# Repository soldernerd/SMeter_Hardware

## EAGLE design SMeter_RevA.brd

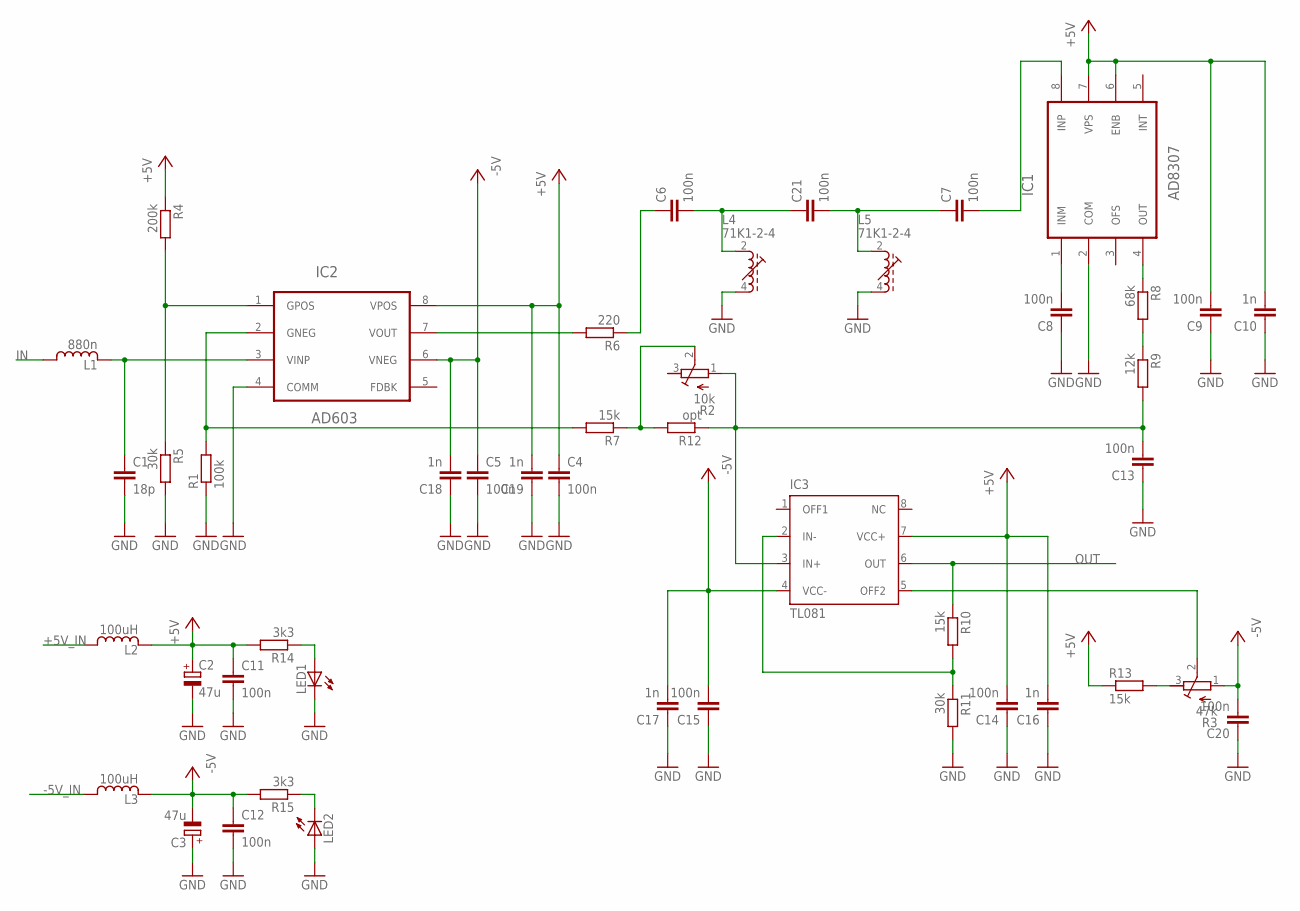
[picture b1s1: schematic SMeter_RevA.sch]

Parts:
C1: 18p; C0805
C2, C3: 47u; SMC_B
C4, C5, C6, C7, C8, C9, C11, C12, C13, C14, C15, C20, C21: 100n; C0805
C10, C16, C17, C18, C19: 1n; C0805
IC1: AD8307; SO8
IC2: AD603; SO8
IC3: TL081; SOIC8
L1: 880n; L0805
L2, L3: 100uH; LPS4018
L4, L5: 71K1-2-4; 71K
LED1, LED2: LED0805
R1: 100k; R0805
R2: 10k; RTRIM3224X
R3: 47k; RTRIM3224X
R4: 200k; R0805
R5, R11: 30k; R0805
R6: 220; R0805
R7, R10, R13: 15k; R0805
R8: 68k; R0805
R9: 12k; R0805
R12: opt; R0805
R14, R15: 3k3; R0805

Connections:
+5V: C2.+, C4.1, C9.2, C10.2, C11.1, C14.2, C16.2, C19.2, IC1.6 (ENB), IC1.7 (VPS), IC2.8 (VPOS), IC3.7 (VCC+), L2.2, R4.1, R13.1, R14.2
+5V_IN: L2.1
-5V: C3.-, C5.1, C12.1, C15.2, C17.2, C18.2, C20.2, IC2.6 (VNEG), IC3.4 (VCC-), L3.2, R3.1 (CCW), R15.2
-5V_IN: L3.1
GND: C1.2, C2.-, C3.+, C4.2, C5.2, C8.1, C9.1, C10.1, C11.2, C12.2, C13.1, C14.1, C15.1, C16.1, C17.1, C18.1, C19.1, C20.1, IC1.2 (COM), IC2.4 (COMM), L4.4 (E), L5.4 (E), LED1.C, LED2.A, R1.1, R5.2, R11.2
IN: L1.1
unnamed: IC2.2 (GNEG), R1.2, R7.2
unnamed: C1.1, IC2.3 (VINP), L1.2
unnamed: IC2.1 (GPOS), R4.2, R5.1
unnamed: IC2.7 (VOUT), R6.2
unnamed: C6.1, R6.1
unnamed: R2.2 (WIPER), R7.1, R12.2
unnamed: C13.2, IC3.3 (IN+), R2.1 (CCW), R9.2, R12.1
unnamed: LED2.C, R15.1
unnamed: LED1.A, R14.1
unnamed: C6.2, C21.1, L4.2 (A)
unnamed: C7.2, IC1.8 (INP)
unnamed: C8.2, IC1.1 (INM)
unnamed: IC1.4 (OUT), R8.1
unnamed: R8.2, R9.1
unnamed: IC3.2 (IN-), R10.2, R11.1
unnamed: R3.3 (CW), R13.2
unnamed: IC3.5 (OFF2), R3.2 (WIPER)
unnamed: C7.1, C21.2, L5.2 (A)
OUT: IC3.6 (OUT), R10.1

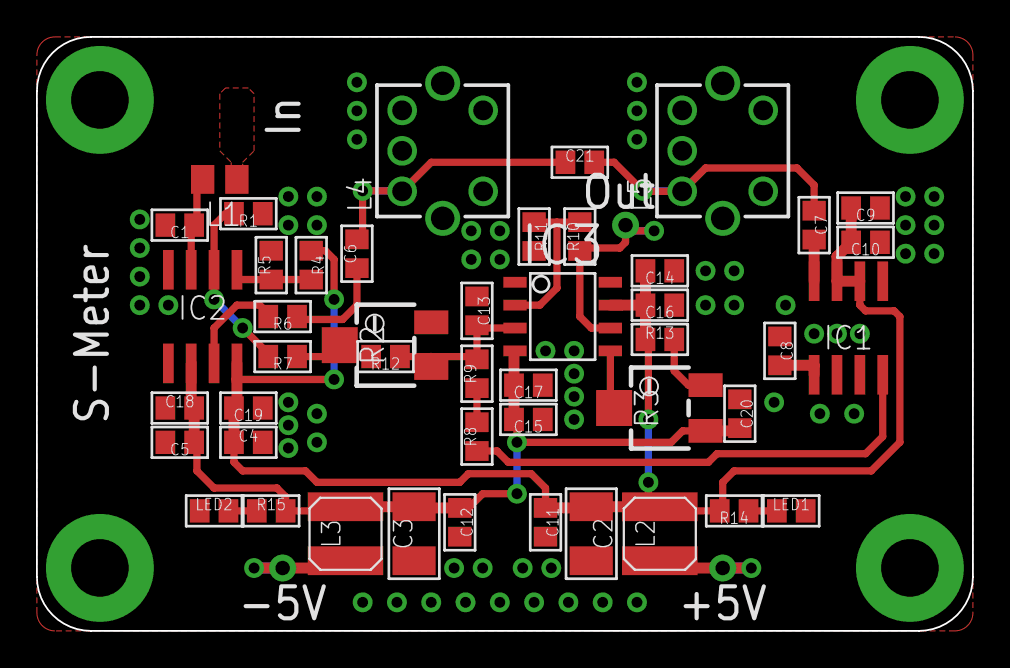
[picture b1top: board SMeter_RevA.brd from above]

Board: 2 copper layers, 52.0 x 33.0 mm, 46 parts (0 on the bottom side), 22 nets.

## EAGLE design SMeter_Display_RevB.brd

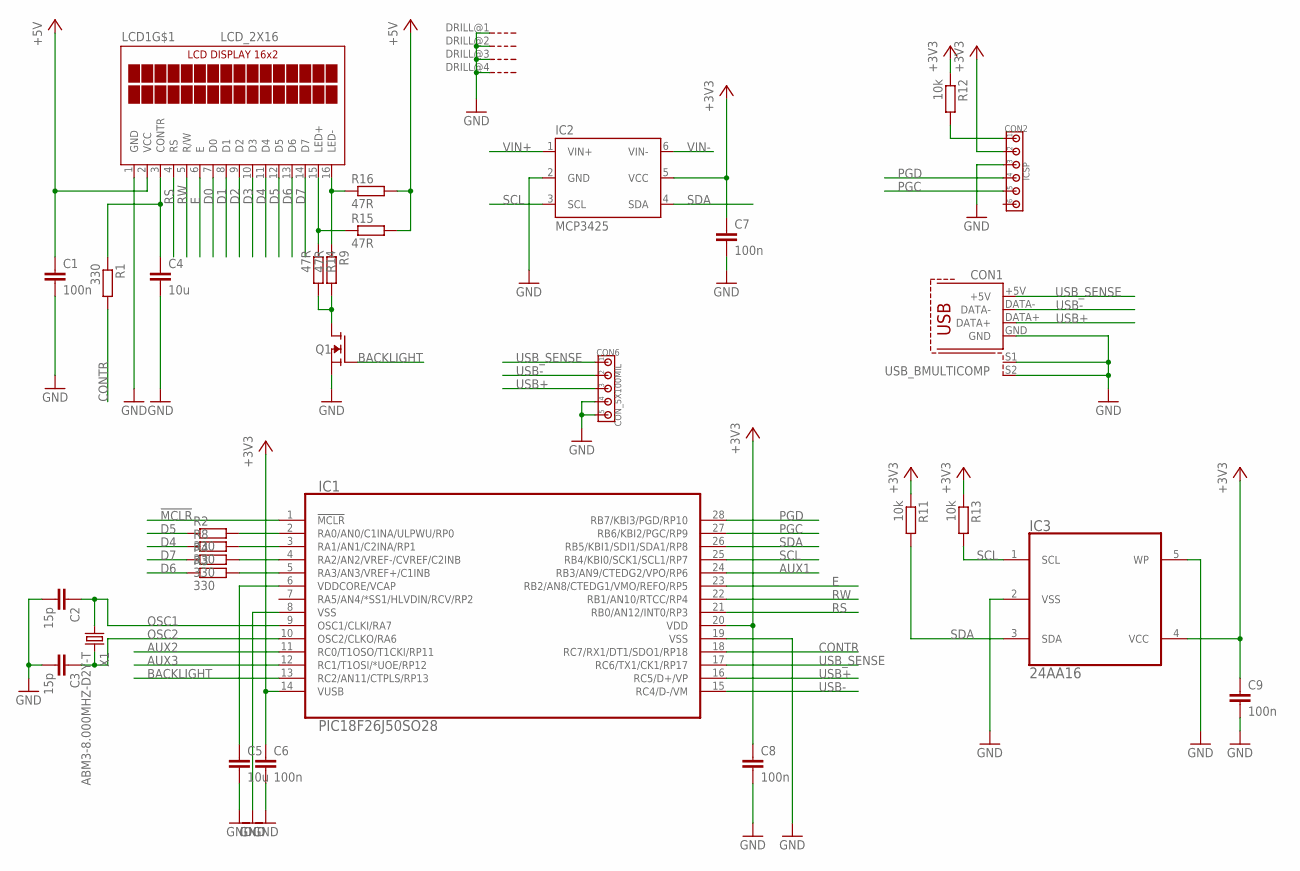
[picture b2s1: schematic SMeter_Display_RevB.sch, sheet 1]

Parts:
C1, C6, C7, C8, C9: 100n; C0805
C2, C3: 15p; C0805
C4, C5: 10u; C0805
CON1: USB_BMULTICOMP; USB_B
CON2: ICSP; 100MIL_6X
CON6: CON_5X100MIL; 100MIL_5X
IC1: PIC18F26J50SO28; SO28W
IC2: MCP3425; SOT-23-6
IC3: 24AA16; SOT-23-5
LCD1: LCD_2X16
Q1: N-FETSOT23; SOT23
R1, R2, R3, R4, R8: 330; R0805
R9, R14, R15, R16: 47R; R0805
R11, R12, R13: 10k; R0805
X1: ABM3-8.000MHZ-D2Y-T; 5X3.2MM

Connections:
!MCLR!: CON2.1, IC1.1 (!MCLR!), R12.2
+3V3: C6.1, C7.1, C8.1, C9.1, CON2.2, IC1.14 (VUSB), IC1.20 (VDD), IC2.5 (VCC), IC3.4 (VCC), R11.1, R12.1, R13.1; also elsewhere on the board
+5V: C1.1, LCD1.2 (VCC), R15.2, R16.2; also elsewhere on the board
AUX1: IC1.24 (RB3/AN9/CTEDG2/VPO/RP6)
AUX2: IC1.11 (RC0/T1OSO/T1CKI/RP11)
AUX3: IC1.12 (RC1/T1OSI/*UOE/RP12)
BACKLIGHT: IC1.13 (RC2/AN11/CTPLS/RP13), Q1.1 (G)
CONTR: IC1.18 (RC7/RX1/DT1/SDO1/RP18), R1.2
D0: LCD1.7 (D0)
D1: LCD1.8 (D1)
D2: LCD1.9 (D2)
D3: LCD1.10 (D3)
D4: LCD1.11 (D4), R8.1
D5: LCD1.12 (D5), R2.1
D6: LCD1.13 (D6), R3.1
D7: LCD1.14 (D7), R4.1
E: IC1.23 (RB2/AN8/CTEDG1/VMO/REFO/RP5), LCD1.6 (E)
GND: C1.2, C2.2, C3.2, C4.2, C5.2, C6.2, C7.2, C8.2, C9.2, CON1.GND, CON1.S1, CON1.S2, CON2.3, CON6.4, CON6.5, IC1.8 (VSS), IC1.19 (VSS), IC2.2 (GND), IC3.2 (VSS), IC3.5 (WP), LCD1.1 (GND), LCD1.DRILL@1 (G), LCD1.DRILL@2 (G), LCD1.DRILL@3 (G), LCD1.DRILL@4 (G), Q1.2 (S); also elsewhere on the board
unnamed: C5.1, IC1.6 (VDDCORE/VCAP)
unnamed: LCD1.16 (LED-), R9.1, R16.1
unnamed: C4.1, LCD1.3 (CONTR), R1.1
unnamed: Q1.3 (D), R9.2, R14.2
unnamed: IC1.2 (RA0/AN0/C1INA/ULPWU/RP0), R2.2
unnamed: IC1.3 (RA1/AN1/C2INA/RP1), R8.2
unnamed: IC1.4 (RA2/AN2/VREF-/CVREF/C2INB), R4.2
unnamed: IC1.5 (RA3/AN3/VREF+/C1INB), R3.2
unnamed: LCD1.15 (LED+), R14.1, R15.1
OSC1: C2.1, IC1.9 (OSC1/CLKI/RA7), X1.1
OSC2: C3.1, IC1.10 (OSC2/CLKO/RA6), X1.2
PGC: CON2.5, IC1.27 (RB6/KBI2/PGC/RP9)
PGD: CON2.4, IC1.28 (RB7/KBI3/PGD/RP10)
RS: IC1.21 (RB0/AN12/INT0/RP3), LCD1.4 (RS)
RW: IC1.22 (RB1/AN10/RTCC/RP4), LCD1.5 (R/W)
SCL: IC1.25 (RB4/KBI0/SCK1/SCL1/RP7), IC2.3 (SCL), IC3.1 (SCL), R13.2
SDA: IC1.26 (RB5/KBI1/SDI1/SDA1/RP8), IC2.4 (SDA), IC3.3 (SDA), R11.2
USB+: CON1.DATA+, CON6.3, IC1.16 (RC5/D+/VP)
USB-: CON1.DATA-, CON6.2, IC1.15 (RC4/D-/VM)
USB_SENSE: CON1.+5V, CON6.1, IC1.17 (RC6/TX1/CK1/RP17)
VIN+: IC2.1 (VIN+); also elsewhere on the board
VIN-: IC2.6 (VIN-); also elsewhere on the board

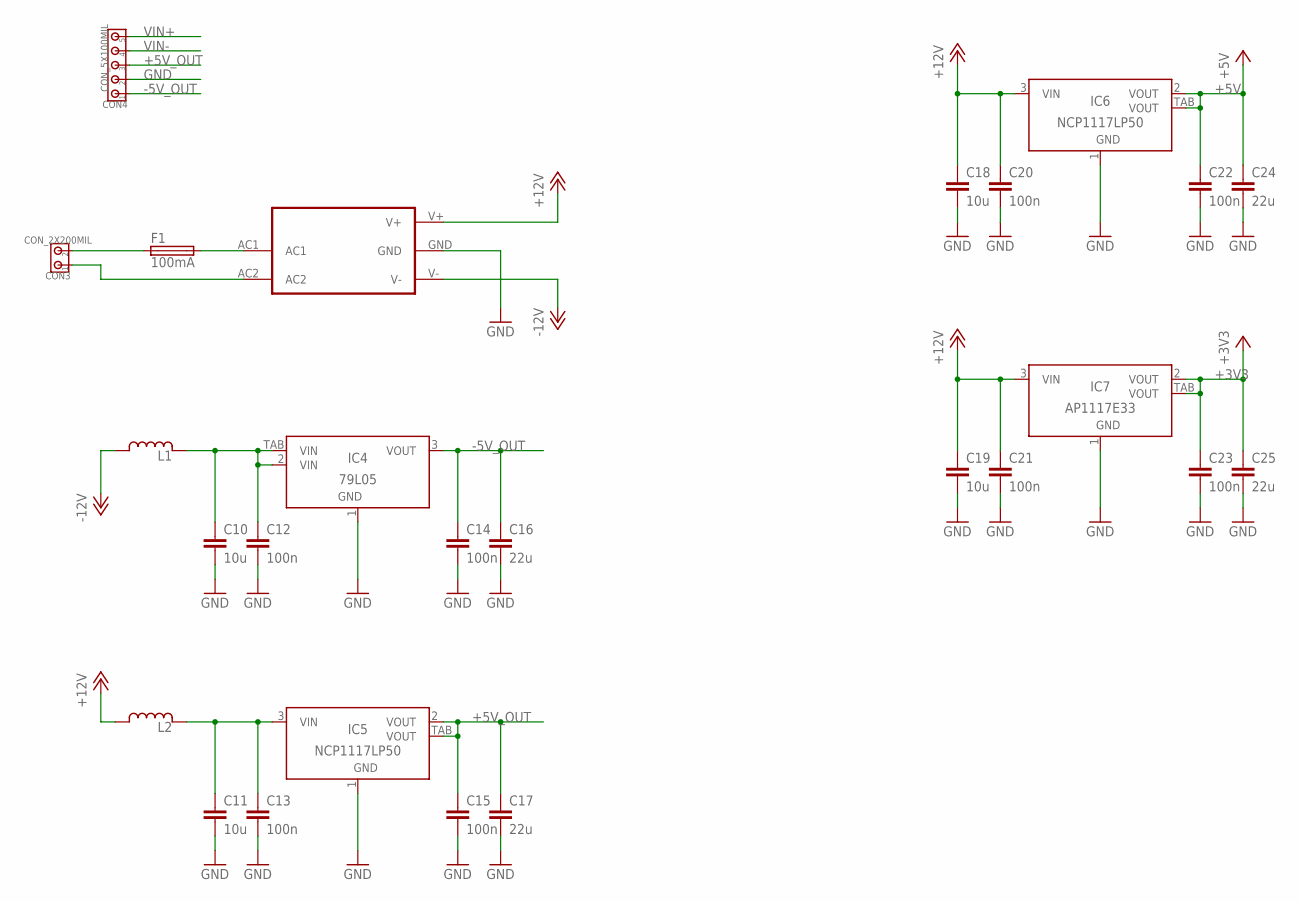
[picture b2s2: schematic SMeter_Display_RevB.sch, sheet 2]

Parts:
ACDC1: MYRRA47247; MYRRA47000
C10, C11, C18, C19: 10u; C1206
C12, C13, C14, C15, C20, C21, C22, C23: 100n; C0805
C16, C17, C24, C25: 22u; C1206
CON3: CON_2X200MIL; 200MIL_2X
CON4: CON_5X100MIL; 100MIL_5X
F1: 100mA; SH22,5
IC4: 79L05; SOT-89
IC5, IC6: NCP1117LP50; SOT223
IC7: AP1117E33; SOT223
L1, L2: INDUCTORLPS4018; LPS4018

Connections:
+3V3: C23.1, C25.1, IC7.2 (VOUT), IC7.TAB (VOUT); also elsewhere on the board
+5V: C22.1, C24.1, IC6.2 (VOUT), IC6.TAB (VOUT); also elsewhere on the board
+5V_OUT: C15.1, C17.1, CON4.3, IC5.2 (VOUT), IC5.TAB (VOUT)
+12V: ACDC1.V+, C18.1, C19.1, C20.1, C21.1, IC6.3 (VIN), IC7.3 (VIN), L2.1
-5V_OUT: C14.1, C16.1, CON4.1, IC4.3 (VOUT)
-12V: ACDC1.V-, L1.1
GND: ACDC1.GND, C10.2, C11.2, C12.2, C13.2, C14.2, C15.2, C16.2, C17.2, C18.2, C19.2, C20.2, C21.2, C22.2, C23.2, C24.2, C25.2, CON4.2, IC4.1 (GND), IC5.1 (GND), IC6.1 (GND), IC7.1 (GND); also elsewhere on the board
unnamed: C10.1, C12.1, IC4.2 (VIN), IC4.TAB (VIN), L1.2
unnamed: C11.1, C13.1, IC5.3 (VIN), L2.2
unnamed: ACDC1.AC1, F1.2
unnamed: ACDC1.AC2, CON3.1
unnamed: CON3.2, F1.1
VIN+: CON4.5; also elsewhere on the board
VIN-: CON4.4; also elsewhere on the board

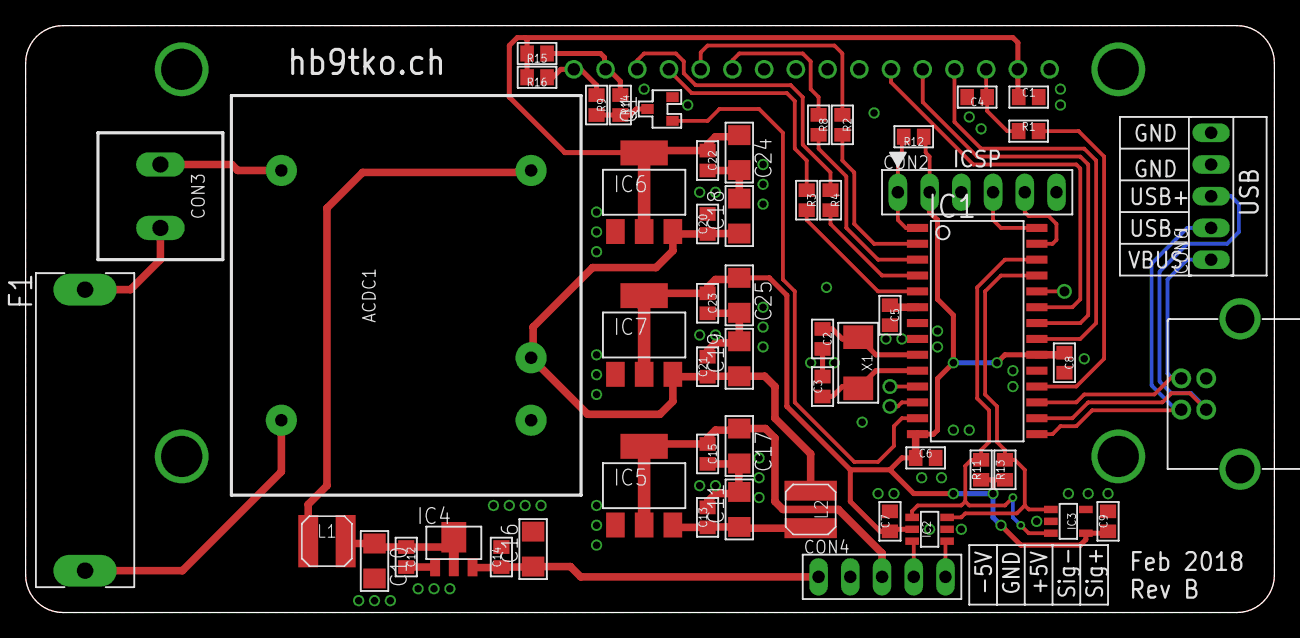
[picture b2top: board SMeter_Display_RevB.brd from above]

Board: 2 copper layers, 100.0 x 47.0 mm, 56 parts (1 on the bottom side), 42 nets.

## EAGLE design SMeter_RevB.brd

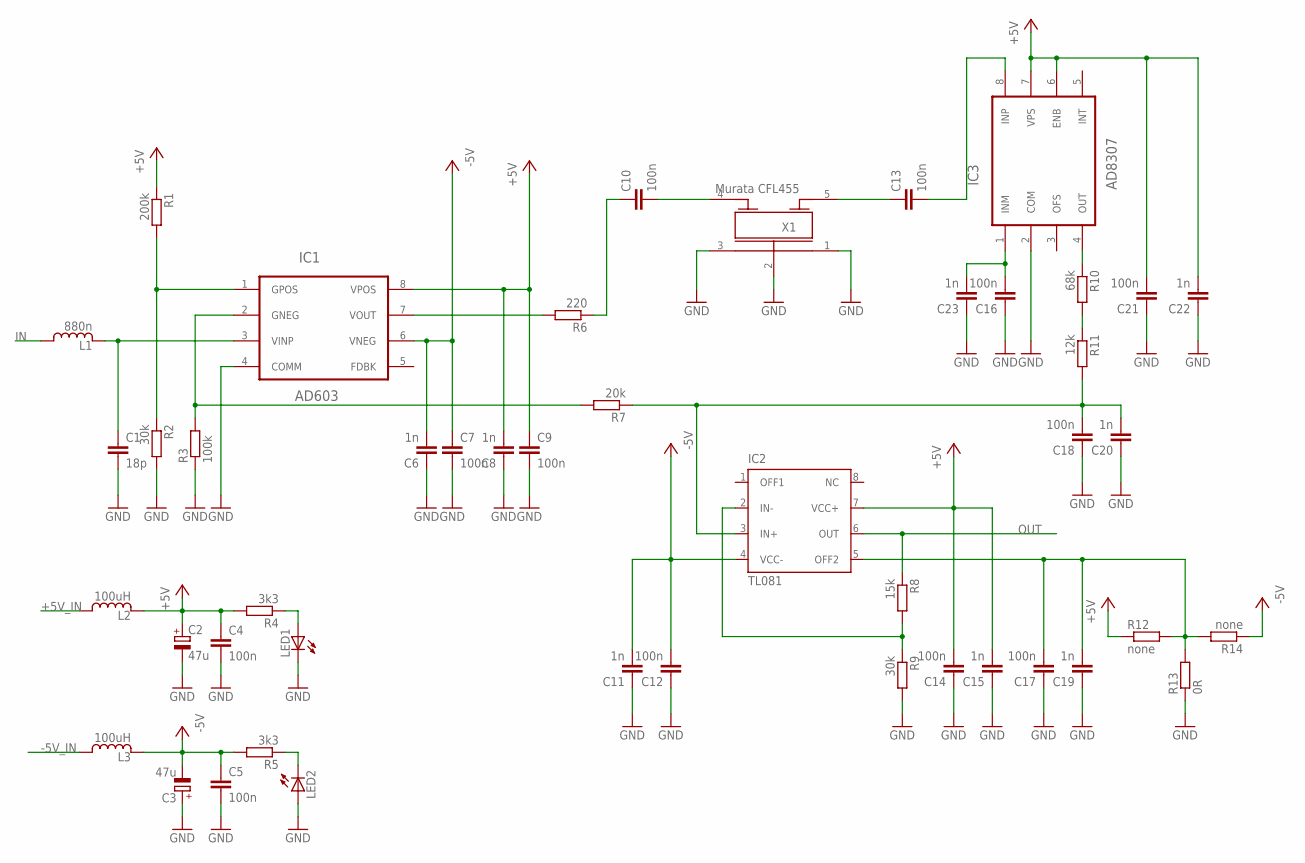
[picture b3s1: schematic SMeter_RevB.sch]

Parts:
C1: 18p; C0805
C2, C3: 47u; SMC_B
C4, C5, C7, C9, C10, C12, C13, C14, C16, C17, C18, C21: 100n; C0805
C6, C8, C11, C15, C19, C20, C22, C23: 1n; C0805
IC1: AD603; SO8
IC2: TL081; SO8
IC3: AD8307; SO8
L1: 880n; L0805
L2, L3: 100uH; LPS4018
LED1, LED2: LED0805
R1: 200k; R0805
R2, R9: 30k; R0805
R3: 100k; R0805
R4, R5: 3k3; R0805
R6: 220; R0805
R7: 20k; R0805
R8: 15k; R0805
R10: 68k; R0805
R11: 12k; R0805
R12, R14: none; R0805
R13: 0R; R0805
X1: Murata CFL455; CFL455

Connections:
+5V: C2.+, C4.1, C8.2, C9.1, C14.2, C15.2, C21.2, C22.2, IC1.8 (VPOS), IC2.7 (VCC+), IC3.6 (ENB), IC3.7 (VPS), L2.2, R1.1, R4.2, R12.1
+5V_IN: L2.1
-5V: C3.-, C5.1, C6.2, C7.1, C11.2, C12.2, IC1.6 (VNEG), IC2.4 (VCC-), L3.2, R5.2, R14.1
-5V_IN: L3.1
GND: C1.2, C2.-, C3.+, C4.2, C5.2, C6.1, C7.2, C8.1, C9.2, C11.1, C12.1, C14.1, C15.1, C16.1, C17.1, C18.1, C19.1, C20.1, C21.1, C22.1, C23.1, IC1.4 (COMM), IC3.2 (COM), LED1.C, LED2.A, R2.2, R3.1, R9.2, R13.1, X1.1, X1.2, X1.3
IN: L1.1
unnamed: IC1.2 (GNEG), R3.2, R7.2
unnamed: C1.1, IC1.3 (VINP), L1.2
unnamed: IC1.1 (GPOS), R1.2, R2.1
unnamed: IC1.7 (VOUT), R6.2
unnamed: C10.1, R6.1
unnamed: C18.2, C20.2, IC2.3 (IN+), R7.1, R11.2
unnamed: LED2.C, R5.1
unnamed: LED1.A, R4.1
unnamed: C10.2, X1.4
unnamed: C13.2, IC3.8 (INP)
unnamed: C16.2, C23.2, IC3.1 (INM)
unnamed: IC3.4 (OUT), R10.1
unnamed: R10.2, R11.1
unnamed: C13.1, X1.5
unnamed: IC2.2 (IN-), R8.2, R9.1
unnamed: C17.2, C19.2, IC2.5 (OFF2), R12.2, R13.2, R14.2
OUT: IC2.6 (OUT), R8.1

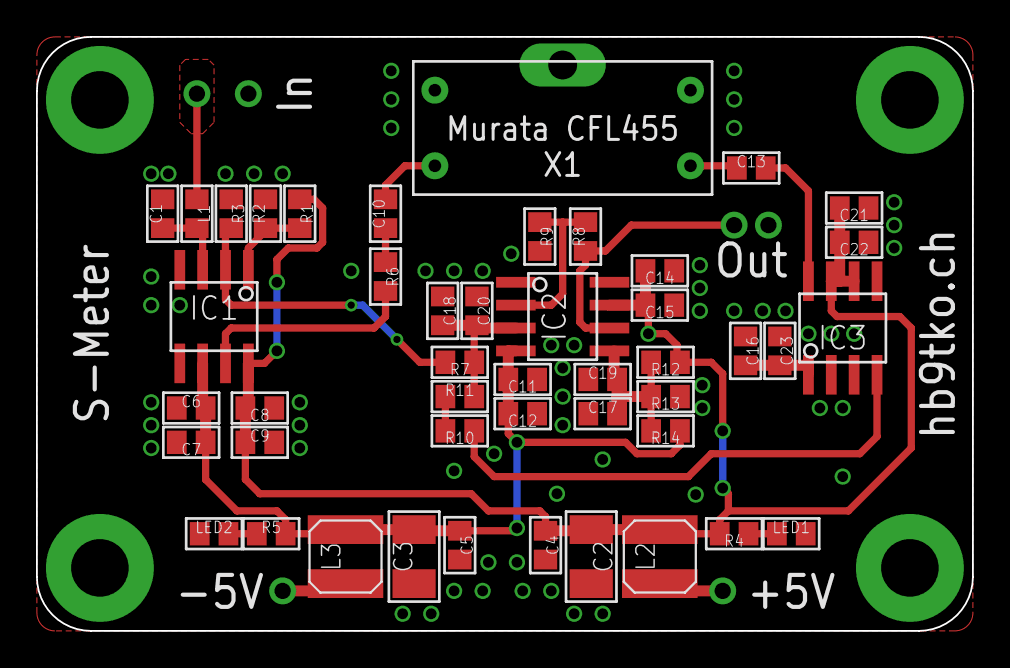
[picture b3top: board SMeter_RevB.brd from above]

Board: 2 copper layers, 52.0 x 33.0 mm, 46 parts (0 on the bottom side), 20 nets.

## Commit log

2018-02-18 Revision B finalized
